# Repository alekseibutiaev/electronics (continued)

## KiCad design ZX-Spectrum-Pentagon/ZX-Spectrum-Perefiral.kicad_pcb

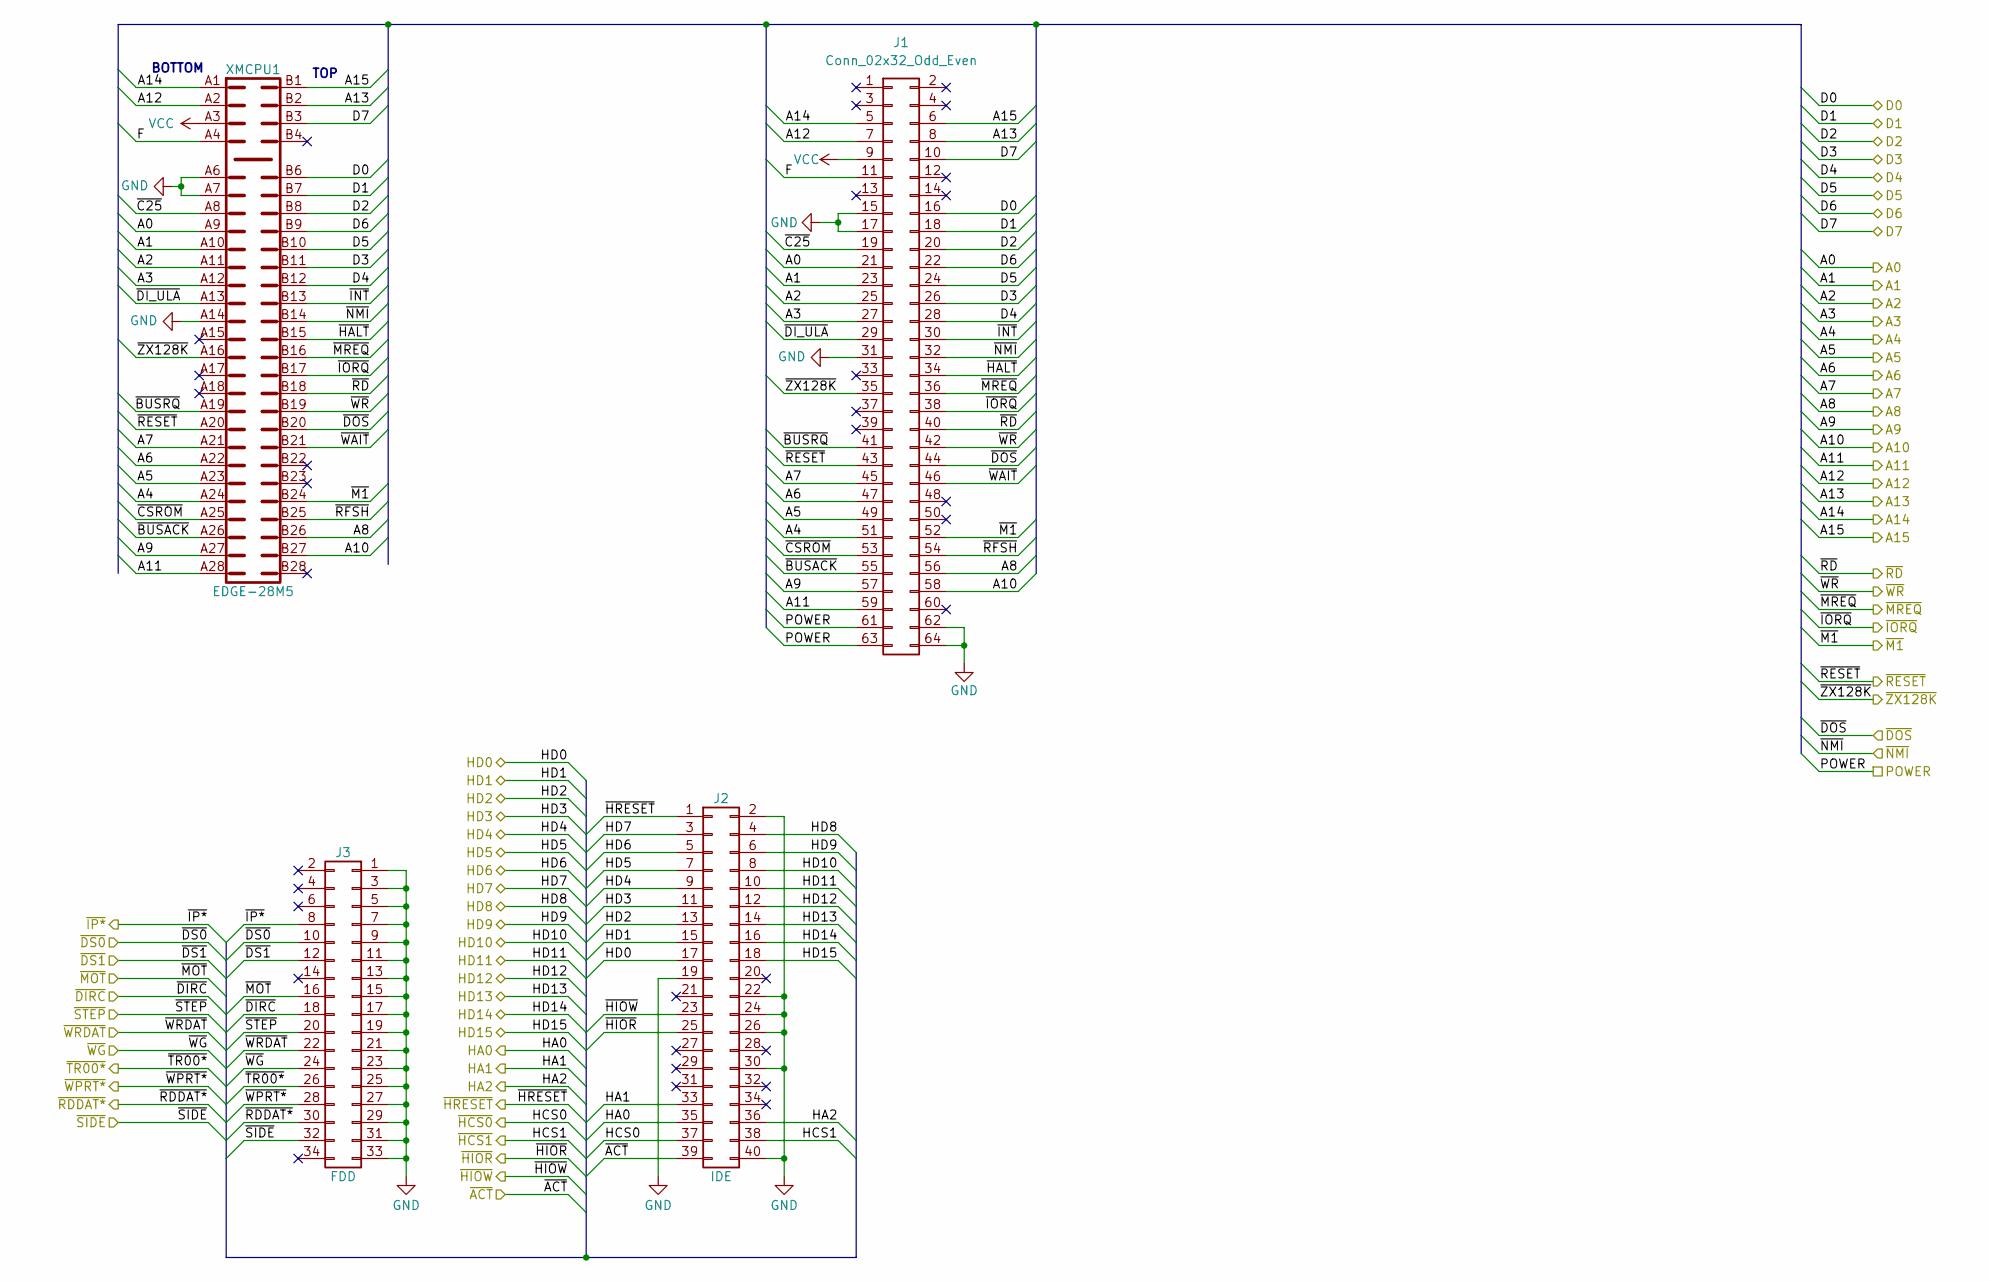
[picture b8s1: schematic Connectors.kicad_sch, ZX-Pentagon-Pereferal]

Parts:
J1: Conn_02x32_Odd_Even; PinSocket_2x32_P2.54mm_Vertical
J2: IDE; IDC-Header_2x20_P2.54mm_Vertical
J3: FDD; IDC-Header_2x17_P2.54mm_Vertical
XMCPU1: EDGE-28M5; EDGE_28M5-2.54

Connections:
/A0: J1.21, XMCPU1.A9; also elsewhere on the board
/A1: J1.23, XMCPU1.A10; also elsewhere on the board
/A2: J1.25, XMCPU1.A11; also elsewhere on the board
/A3: J1.27, XMCPU1.A12; also elsewhere on the board
/A4: J1.51, XMCPU1.A24; also elsewhere on the board
/A5: J1.49, XMCPU1.A23; also elsewhere on the board
/A6: J1.47, XMCPU1.A22; also elsewhere on the board
/A7: J1.45, XMCPU1.A21; also elsewhere on the board
/A8: J1.56, XMCPU1.B26; also elsewhere on the board
/A9: J1.57, XMCPU1.A27; also elsewhere on the board
/A10: J1.58, XMCPU1.B27; also elsewhere on the board
/A11: J1.59, XMCPU1.A28; also elsewhere on the board
/A12: J1.7, XMCPU1.A2; also elsewhere on the board
/A13: J1.8, XMCPU1.B2; also elsewhere on the board
/A14: J1.5, XMCPU1.A1; also elsewhere on the board
/A15: J1.6, XMCPU1.B1; also elsewhere on the board
/Connectors/F: J1.11, XMCPU1.A4
/Connectors/~BUSACK: J1.55, XMCPU1.A26
/Connectors/~BUSRQ: J1.41, XMCPU1.A19
/Connectors/~C25: J1.19, XMCPU1.A8
/Connectors/~CSROM: J1.53, XMCPU1.A25
/Connectors/~DI_ULA: J1.29, XMCPU1.A13
/Connectors/~HALT: J1.34, XMCPU1.B15
/Connectors/~INT: J1.30, XMCPU1.B13
/Connectors/~RFSH: J1.54, XMCPU1.B25
/Connectors/~WAIT: J1.46, XMCPU1.B21
/D0: J1.16, XMCPU1.B6; also elsewhere on the board
/D1: J1.18, XMCPU1.B7; also elsewhere on the board
/D2: J1.20, XMCPU1.B8; also elsewhere on the board
/D3: J1.26, XMCPU1.B11; also elsewhere on the board
/D4: J1.28, XMCPU1.B12; also elsewhere on the board
/D5: J1.24, XMCPU1.B10; also elsewhere on the board
/D6: J1.22, XMCPU1.B9; also elsewhere on the board
/D7: J1.10, XMCPU1.B3; also elsewhere on the board
/HA0: J2.35; also elsewhere on the board
/HA1: J2.33; also elsewhere on the board
/HA2: J2.36; also elsewhere on the board
/HD0: J2.17; also elsewhere on the board
/HD1: J2.15; also elsewhere on the board
/HD2: J2.13; also elsewhere on the board
/HD3: J2.11; also elsewhere on the board
/HD4: J2.9; also elsewhere on the board
/HD5: J2.7; also elsewhere on the board
/HD6: J2.5; also elsewhere on the board
/HD7: J2.3; also elsewhere on the board
/HD8: J2.4; also elsewhere on the board
/HD9: J2.6; also elsewhere on the board
/HD10: J2.8; also elsewhere on the board
/HD11: J2.10; also elsewhere on the board
/HD12: J2.12; also elsewhere on the board
/HD13: J2.14; also elsewhere on the board
/HD14: J2.16; also elsewhere on the board
/HD15: J2.18; also elsewhere on the board
/~ACT: J2.39; also elsewhere on the board
/~DIRC: J3.18; also elsewhere on the board
/~DOS: J1.44, XMCPU1.B20; also elsewhere on the board
/~DS0: J3.10; also elsewhere on the board
/~DS1: J3.12; also elsewhere on the board
/~HCS0: J2.37; also elsewhere on the board
/~HCS1: J2.38; also elsewhere on the board
/~HIOR: J2.25; also elsewhere on the board
/~HIOW: J2.23; also elsewhere on the board
/~HRESET: J2.1; also elsewhere on the board
/~IORQ: J1.38, XMCPU1.B17; also elsewhere on the board
/~IP*: J3.8; also elsewhere on the board
/~M1: J1.52, XMCPU1.B24; also elsewhere on the board
/~MOT: J3.16; also elsewhere on the board
/~MREQ: J1.36, XMCPU1.B16; also elsewhere on the board
/~NMI: J1.32, XMCPU1.B14; also elsewhere on the board
/~RDDAT*: J3.30; also elsewhere on the board
/~RD: J1.40, XMCPU1.B18; also elsewhere on the board
/~RESET: J1.43, XMCPU1.A20; also elsewhere on the board
/~SIDE: J3.32; also elsewhere on the board
/~STEP: J3.20; also elsewhere on the board
/~TR00*: J3.26; also elsewhere on the board
/~WG: J3.24; also elsewhere on the board
/~WPRT*: J3.28; also elsewhere on the board
/~WRDAT: J3.22; also elsewhere on the board
/~WR: J1.42, XMCPU1.B19; also elsewhere on the board
/~ZX128: J1.35, XMCPU1.A16; also elsewhere on the board
GND: J1.15, J1.17, J1.31, J1.62, J1.64, J2.2, J2.19, J2.22, J2.24, J2.26, J2.30, J2.40, J3.1, J3.3, J3.5, J3.7, J3.9, J3.11, J3.13, J3.15, J3.17, J3.19, J3.21, J3.23, J3.25, J3.27, J3.29, J3.31, J3.33, XMCPU1.A6, XMCPU1.A7, XMCPU1.A14; also elsewhere on the board
POWER: J1.61, J1.63; also elsewhere on the board
VCC: J1.9, XMCPU1.A3; also elsewhere on the board

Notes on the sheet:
TOP
BOTTOM

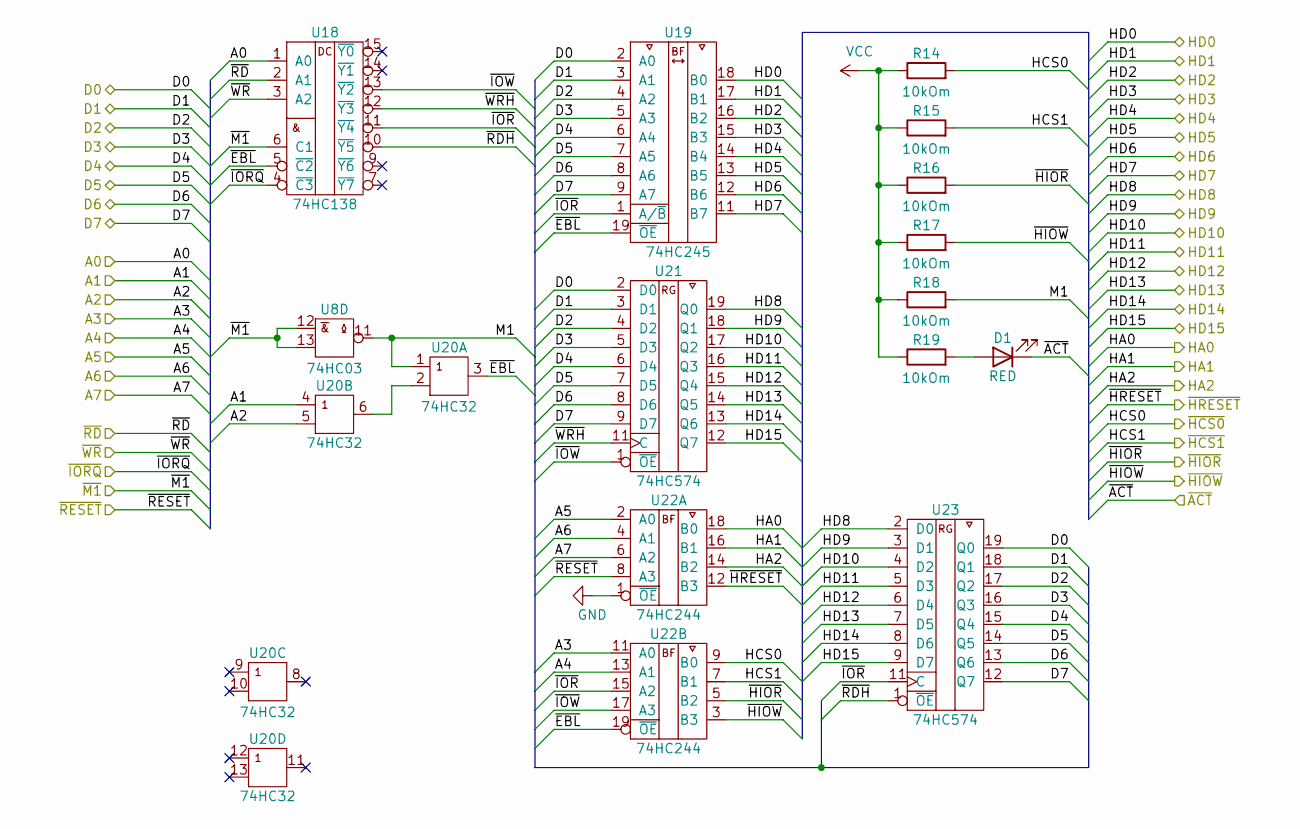
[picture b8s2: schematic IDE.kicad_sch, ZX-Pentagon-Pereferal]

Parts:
D1: RED; D_0805_2012Metric
R14, R15, R16, R17, R18, R19: 10kOm; R_0805_2012Metric
U8: 74HC03; DIP-14_W7.62mm
U18: 74HC138; DIP-16_W7.62mm
U19: 74HC245; DIP-20_W7.62mm
U20: 74HC32; DIP-14_W7.62mm
U21, U23: 74HC574; DIP-20_W7.62mm
U22: 74HC244; DIP-20_W7.62mm

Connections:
/A0: U18.1 (A0); also elsewhere on the board
/A1: U20.4 (A); also elsewhere on the board
/A2: U20.5 (B); also elsewhere on the board
/A3: U22.11 (A0); also elsewhere on the board
/A4: U22.13 (A1); also elsewhere on the board
/A5: U22.2 (A0); also elsewhere on the board
/A6: U22.4 (A1); also elsewhere on the board
/A7: U22.6 (A2); also elsewhere on the board
/D0: U19.2 (A0), U21.2 (D0), U23.19 (Q0); also elsewhere on the board
/D1: U19.3 (A1), U21.3 (D1), U23.18 (Q1); also elsewhere on the board
/D2: U19.4 (A2), U21.4 (D2), U23.17 (Q2); also elsewhere on the board
/D3: U19.5 (A3), U21.5 (D3), U23.16 (Q3); also elsewhere on the board
/D4: U19.6 (A4), U21.6 (D4), U23.15 (Q4); also elsewhere on the board
/D5: U19.7 (A5), U21.7 (D5), U23.14 (Q5); also elsewhere on the board
/D6: U19.8 (A6), U21.8 (D6), U23.13 (Q6); also elsewhere on the board
/D7: U19.9 (A7), U21.9 (D7), U23.12 (Q7); also elsewhere on the board
/HA0: U22.18 (B0); also elsewhere on the board
/HA1: U22.16 (B1); also elsewhere on the board
/HA2: U22.14 (B2); also elsewhere on the board
/HD0: U19.18 (B0); also elsewhere on the board
/HD1: U19.17 (B1); also elsewhere on the board
/HD2: U19.16 (B2); also elsewhere on the board
/HD3: U19.15 (B3); also elsewhere on the board
/HD4: U19.14 (B4); also elsewhere on the board
/HD5: U19.13 (B5); also elsewhere on the board
/HD6: U19.12 (B6); also elsewhere on the board
/HD7: U19.11 (B7); also elsewhere on the board
/HD8: U21.19 (Q0), U23.2 (D0); also elsewhere on the board
/HD9: U21.18 (Q1), U23.3 (D1); also elsewhere on the board
/HD10: U21.17 (Q2), U23.4 (D2); also elsewhere on the board
/HD11: U21.16 (Q3), U23.5 (D3); also elsewhere on the board
/HD12: U21.15 (Q4), U23.6 (D4); also elsewhere on the board
/HD13: U21.14 (Q5), U23.7 (D5); also elsewhere on the board
/HD14: U21.13 (Q6), U23.8 (D6); also elsewhere on the board
/HD15: U21.12 (Q7), U23.9 (D7); also elsewhere on the board
/IDE/M1: R18.2, U8.11 (~Y), U20.1 (A)
/IDE/~EBL: U18.5 (~C2), U19.19 (~OE), U20.3 (Y), U22.19 (~OE)
/IDE/~IOR: U18.11 (~Y4), U19.1 (A/~B), U22.15 (A2), U23.11 (C)
/IDE/~IOW: U18.13 (~Y2), U21.1 (~OE), U22.17 (A3)
/IDE/~RDH: U18.10 (~Y5), U23.1 (~OE)
/IDE/~WRH: U18.12 (~Y3), U21.11 (C)
/~ACT: D1.1 (K); also elsewhere on the board
/~HCS0: R14.2, U22.9 (B0); also elsewhere on the board
/~HCS1: R15.2, U22.7 (B1); also elsewhere on the board
/~HIOR: R16.2, U22.5 (B2); also elsewhere on the board
/~HIOW: R17.2, U22.3 (B3); also elsewhere on the board
/~HRESET: U22.12 (B3); also elsewhere on the board
/~IORQ: U18.4 (~C3); also elsewhere on the board
/~M1: U8.12 (A), U8.13 (B), U18.6 (C1); also elsewhere on the board
/~RD: U18.2 (A1); also elsewhere on the board
/~RESET: U22.8 (A3); also elsewhere on the board
/~WR: U18.3 (A2); also elsewhere on the board
GND: U8.7 (GND), U18.8 (GND), U19.10 (GND), U20.7 (GND), U21.10 (GND), U22.1 (~OE), U22.10 (GND), U23.10 (GND); also elsewhere on the board
unnamed: D1.2 (A), R19.2
unnamed: U20.2 (B), U20.6 (Y)
VCC: R14.1, R15.1, R16.1, R17.1, R18.1, R19.1, U8.14 (VCC), U18.16 (VCC), U19.20 (VCC), U20.14 (VCC), U21.20 (VCC), U22.20 (VCC), U23.20 (VCC); also elsewhere on the board

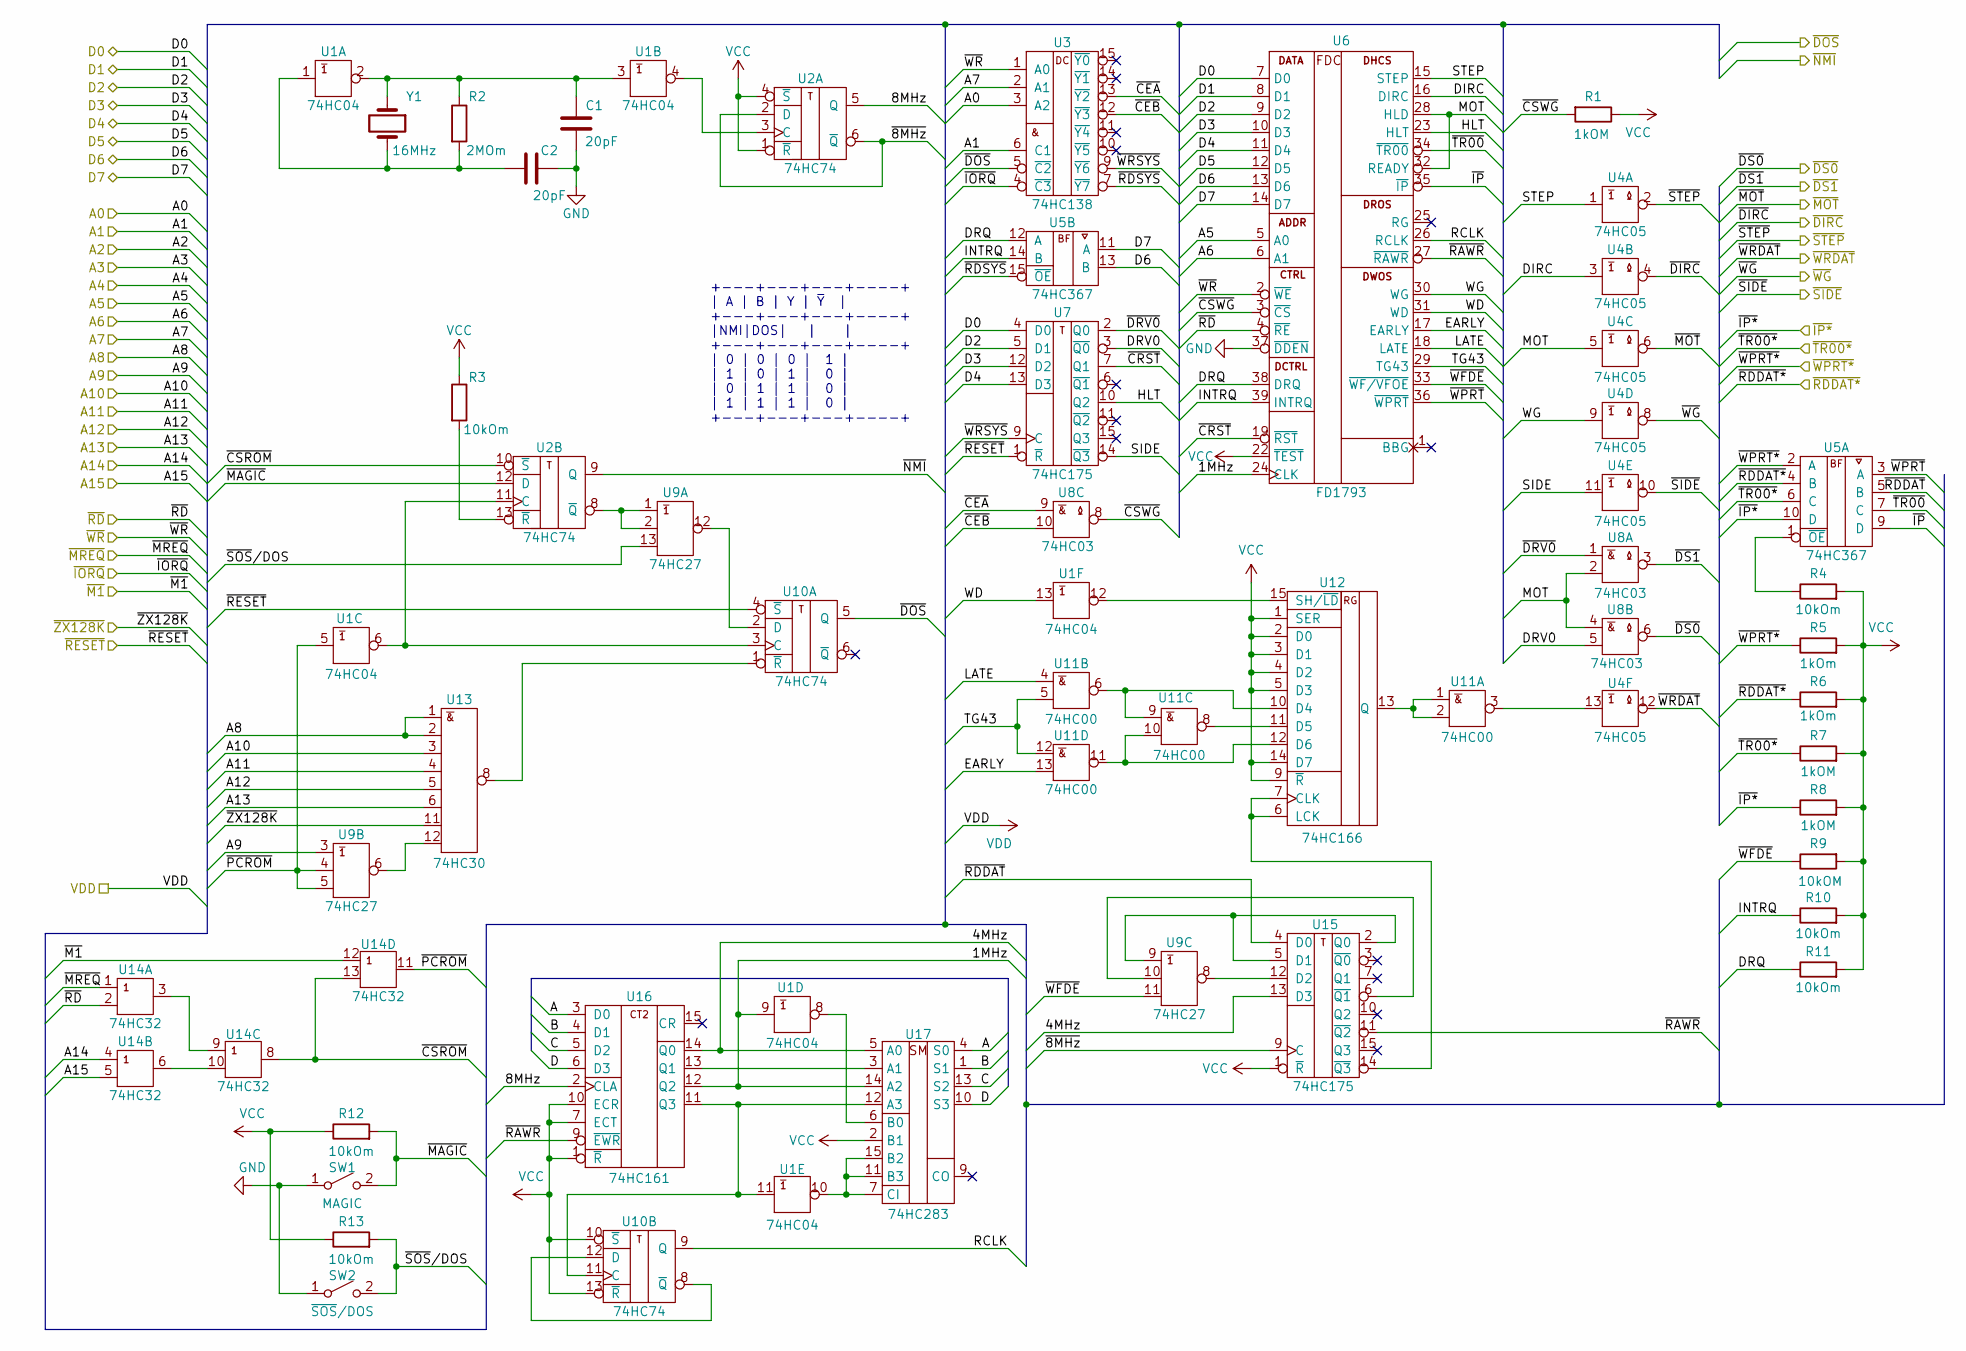
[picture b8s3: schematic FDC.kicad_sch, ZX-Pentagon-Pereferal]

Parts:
C1, C2: 20pF; C_0805_2012Metric_Pad1.18x1.45mm_HandSolder
R1, R7, R8: 1kOM; R_0805_2012Metric
R2: 2MOm; R_0805_2012Metric_Pad1.20x1.40mm_HandSolder
R3, R4, R10, R11, R12, R13: 10kOm; R_0805_2012Metric
R5, R6: 1kOm; R_0805_2012Metric
R9: 10kOM; R_0805_2012Metric
SW1: MAGIC; SW_Tactile_SPST_Angled_PTS645Vx39-2LFS
SW2: ~{SOS}/DOS; SW_Tactile_SPST_Angled_PTS645Vx39-2LFS
U1: 74HC04; DIP-14_W7.62mm
U2, U10: 74HC74; DIP-14_W7.62mm
U3: 74HC138; DIP-16_W7.62mm
U4: 74HC05; DIP-14_W7.62mm
U5: 74HC367; DIP-16_W7.62mm
U6: FD1793; DIP-40_W15.24mm
U7, U15: 74HC175; DIP-16_W7.62mm
U8: 74HC03; DIP-14_W7.62mm
U9: 74HC27; DIP-14_W7.62mm
U11: 74HC00; DIP-14_W7.62mm
U12: 74HC166; DIP-16_W7.62mm
U13: 74HC30; DIP-14_W7.62mm
U14: 74HC32; DIP-14_W7.62mm
U16: 74HC161; DIP-16_W7.62mm
U17: 74HC283; DIP-16_W7.62mm
Y1: 16MHz; Crystal_HC49-U_Vertical

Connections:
/A0: U3.3 (A2); also elsewhere on the board
/A1: U3.6 (C1); also elsewhere on the board
/A5: U6.5 (A0); also elsewhere on the board
/A6: U6.6 (A1); also elsewhere on the board
/A7: U3.2 (A1); also elsewhere on the board
/A8: U13.1 (A), U13.2 (B); also elsewhere on the board
/A9: U9.3 (A); also elsewhere on the board
/A10: U13.3 (C); also elsewhere on the board
/A11: U13.4 (D); also elsewhere on the board
/A12: U13.5 (E); also elsewhere on the board
/A13: U13.6 (F); also elsewhere on the board
/A14: U14.4 (A); also elsewhere on the board
/A15: U14.5 (B); also elsewhere on the board
/D0: U6.7 (D0), U7.4 (D0); also elsewhere on the board
/D1: U6.8 (D1); also elsewhere on the board
/D2: U6.9 (D2), U7.5 (D1); also elsewhere on the board
/D3: U6.10 (D3), U7.12 (D2); also elsewhere on the board
/D4: U6.11 (D4), U7.13 (D3); also elsewhere on the board
/D5: U6.12 (D5); also elsewhere on the board
/D6: U5.13 (B), U6.13 (D6); also elsewhere on the board
/D7: U5.11 (A), U6.14 (D7); also elsewhere on the board
/FDC/1MHz: U1.9 (A), U6.24 (CLK), U16.12 (Q2), U17.14 (A2)
/FDC/4MHz: U15.13 (D3), U16.14 (Q0), U17.5 (A0)
/FDC/8MHz: U2.5 (Q), U16.2 (CLA)
/FDC/A: U16.3 (D0), U17.4 (S0)
/FDC/B: U16.4 (D1), U17.1 (S1)
/FDC/C: U16.5 (D2), U17.13 (S2)
/FDC/D: U16.6 (D3), U17.10 (S3)
/FDC/DIRC: U4.3 (A), U6.16 (DIRC)
/FDC/DRQ: R11.1, U5.12 (A), U6.38 (DRQ)
/FDC/DRV0: U7.3 (~Q0), U8.5 (B)
/FDC/EARLY: U6.17 (EARLY), U11.13 (B)
/FDC/HLT: U6.23 (HLT), U7.10 (Q2)
/FDC/INTRQ: R10.1, U5.14 (B), U6.39 (INTRQ)
/FDC/LATE: U6.18 (LATE), U11.4 (A)
/FDC/MOT: U4.5 (A), U6.28 (HLD), U6.32 (READY), U8.2 (B), U8.4 (A)
/FDC/RCLK: U6.26 (RCLK), U10.9 (Q)
/FDC/SIDE: U4.11 (A), U7.14 (~Q3)
/FDC/STEP: U4.1 (A), U6.15 (STEP)
/FDC/TG43: U6.29 (TG43), U11.5 (B), U11.12 (A)
/FDC/WD: U1.13 (A), U6.31 (WD)
/FDC/WG: U4.9 (A), U6.30 (WG)
/FDC/~8MHz: U2.2 (D), U2.6 (~Q), U15.9 (C)
/FDC/~CEA: U3.13 (~Y2), U8.9 (A)
/FDC/~CEB: U3.12 (~Y3), U8.10 (B)
/FDC/~CRST: U6.19 (~RST), U7.7 (Q1)
/FDC/~CSROM: U2.10 (~S), U14.8 (Y), U14.13 (B)
/FDC/~CSWG: R1.2, U6.3 (~CS), U8.8 (~Y)
/FDC/~DRV0: U7.2 (Q0), U8.1 (A)
/FDC/~IP: U5.9 (D), U6.35 (~IP)
/FDC/~MAGIC: R12.2, SW1.2 (B), U2.12 (D)
/FDC/~PCROM: U1.5 (A), U9.4 (B), U9.5 (C), U14.11 (Y)
/FDC/~RAWR: U6.27 (~RAWR), U15.11 (~Q2), U16.9 (~EWR)
/FDC/~RDDAT: U5.5 (B), U15.4 (D0)
/FDC/~RDSYS: U3.7 (~Y7), U5.15 (~OE)
/FDC/~SOS/DOS: R13.2, SW2.2 (B), U9.13 (C)
/FDC/~TR00: U5.7 (C), U6.34 (~TR00)
/FDC/~WFDE: R9.1, U6.33 (~WF/VFOE), U9.11 (C)
/FDC/~WPRT: U5.3 (A), U6.36 (~WPRT)
/FDC/~WRSYS: U3.9 (~Y6), U7.9 (C)
/~DIRC: U4.4 (~Y); also elsewhere on the board
/~DOS: U3.5 (~C2), U10.5 (Q); also elsewhere on the board
/~DS0: U8.6 (~Y); also elsewhere on the board
/~DS1: U8.3 (~Y); also elsewhere on the board
/~IORQ: U3.4 (~C3); also elsewhere on the board
/~IP*: R8.1, U5.10 (D); also elsewhere on the board
/~M1: U14.12 (A); also elsewhere on the board
/~MOT: U4.6 (~Y); also elsewhere on the board
/~MREQ: U14.1 (A); also elsewhere on the board
/~NMI: U2.9 (Q); also elsewhere on the board
/~RDDAT*: R6.1, U5.4 (B); also elsewhere on the board
/~RD: U6.4 (~RE), U14.2 (B); also elsewhere on the board
/~RESET: U7.1 (~R), U10.4 (~S); also elsewhere on the board
/~SIDE: U4.10 (~Y); also elsewhere on the board
/~STEP: U4.2 (~Y); also elsewhere on the board
/~TR00*: R7.1, U5.6 (C); also elsewhere on the board
/~WG: U4.8 (~Y); also elsewhere on the board
/~WPRT*: R5.1, U5.2 (A); also elsewhere on the board
/~WRDAT: U4.12 (~Y); also elsewhere on the board
/~WR: U3.1 (A0), U6.2 (~WE); also elsewhere on the board
/~ZX128: U13.11 (G); also elsewhere on the board
GND: C1.2, C2.2, SW1.1 (A), SW2.1 (A), U1.7 (GND), U2.7 (GND), U3.8 (GND), U4.7 (GND), U5.8 (GND), U6.20 (GND), U6.37 (~DDEN), U7.8 (GND), U8.7 (GND), U9.7 (GND), U10.7 (GND), U11.7 (GND), U12.8 (GND), U13.7 (GND), U14.7 (GND), U15.8 (GND), U16.8 (GND), U17.8 (GND); also elsewhere on the board
unnamed: C2.1, R2.2, U1.1 (A), Y1.2
unnamed: C1.1, R2.1, U1.2 (~Y), U1.3 (A), Y1.1
unnamed: U1.4 (~Y), U2.3 (C)
unnamed: U2.8 (~Q), U9.1 (A), U9.2 (B)
unnamed: R3.2, U2.13 (~R)
unnamed: R4.1, U5.1 (~OE)
unnamed: U1.6 (~Y), U2.11 (C), U10.3 (C)
unnamed: U9.12 (~Y), U10.2 (D)
unnamed: U10.1 (~R), U13.8 (~Y)
unnamed: U1.11 (A), U10.11 (C), U16.11 (Q3), U17.12 (A3)
unnamed: U10.8 (~Q), U10.12 (D)
unnamed: U11.1 (A), U11.2 (B), U12.13 (Q)
unnamed: U4.13 (A), U11.3 (~Y)
unnamed: U11.6 (~Y), U11.9 (A), U12.10 (D4)
unnamed: U11.10 (B), U11.11 (~Y), U12.12 (D6)
unnamed: U11.8 (~Y), U12.11 (D5)
unnamed: U12.6 (LCK), U12.7 (CLK), U15.14 (~Q3)
unnamed: U1.12 (~Y), U12.15 (SH/~LD)
unnamed: U9.6 (~Y), U13.12 (H)
unnamed: U14.3 (Y), U14.9 (A)
unnamed: U14.6 (Y), U14.10 (B)
unnamed: U9.9 (A), U15.2 (Q0), U15.5 (D1)
unnamed: U9.8 (~Y), U15.12 (D2)
unnamed: U9.10 (B), U15.6 (~Q1)
unnamed: U16.13 (Q1), U17.3 (A1)
unnamed: U1.8 (~Y), U17.6 (B0)
unnamed: U1.10 (~Y), U17.7 (CI), U17.11 (B3), U17.15 (B2)
VCC: R1.1, R3.1, R4.2, R5.2, R6.2, R7.2, R8.2, R9.2, R10.2, R11.2, R12.1, R13.1, U1.14 (VCC), U2.1 (~R), U2.4 (~S), U2.14 (VCC), U3.16 (VCC), U4.14 (VCC), U5.16 (VCC), U6.21 (VCC), U6.22 (~TEST), U7.16 (VCC), U8.14 (VCC), U9.14 (VCC), U10.10 (~S), U10.13 (~R), U10.14 (VCC), U11.14 (VCC), U12.1 (SER), U12.2 (D0), U12.3 (D1), U12.4 (D2), U12.5 (D3), U12.9 (~R), U12.14 (D7), U12.16 (VCC), U13.14 (VCC), U14.14 (VCC), U15.1 (~R), U15.16 (VCC), U16.1 (~R), U16.7 (ECT), U16.10 (ECR), U16.16 (VCC), U17.2 (B1), U17.16 (VCC); also elsewhere on the board
VDD: U6.40 (VDD); also elsewhere on the board

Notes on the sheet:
+---+---+---+----+ | A | B | Y | ~{Y} | +---+---+---+----+ |NMI|DOS| | | +---+---+---+----+ | 0 | 0 | 0 | 1 | | 1 | 0 | 1 | 0 | | 0 | 1 | 1 | 0 | | 1 | 1 | 1 | 0 | +---+---+---+----+

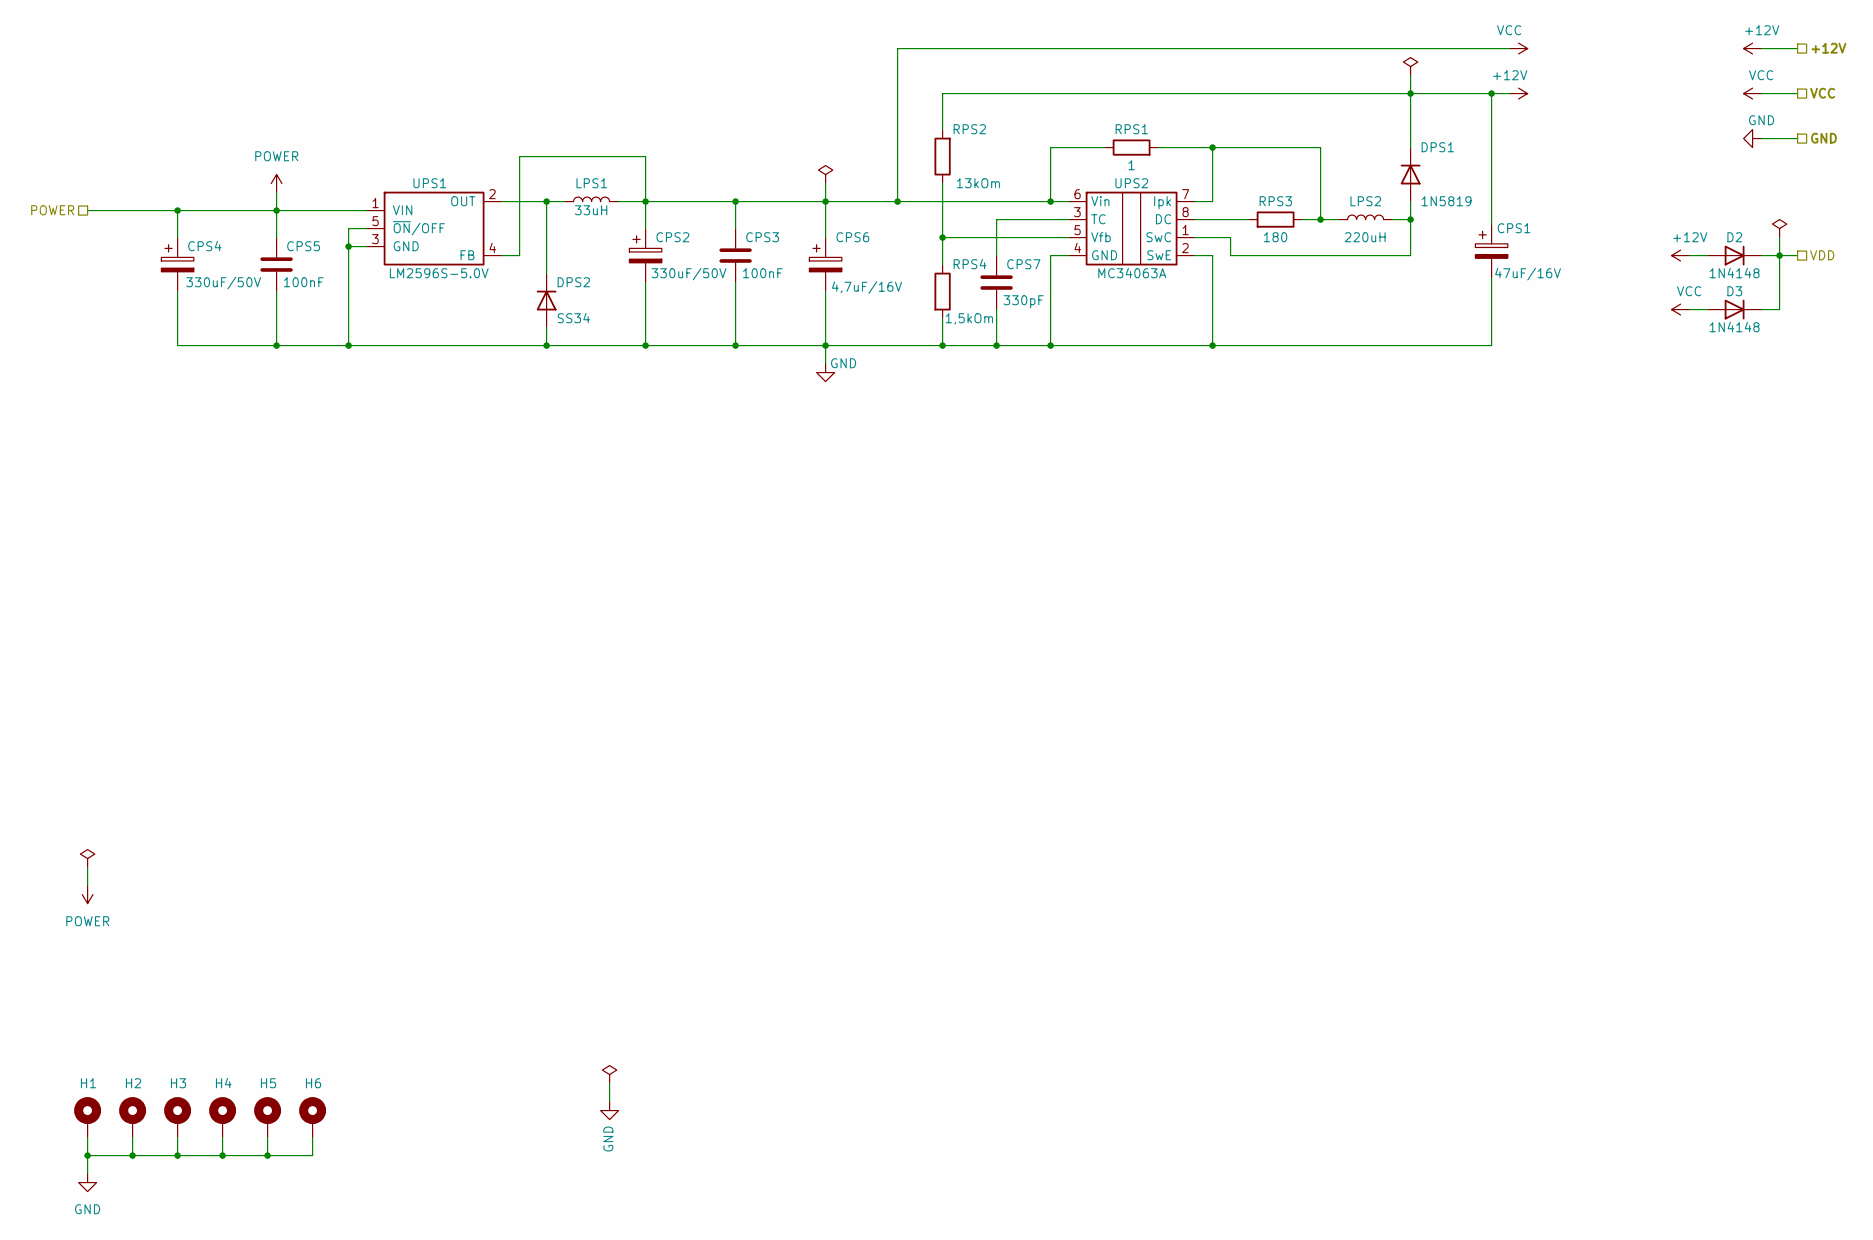
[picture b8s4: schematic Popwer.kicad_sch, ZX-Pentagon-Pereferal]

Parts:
CPS1: 47uF/16V; CP_EIA-3216-18_Kemet-A_Pad1.58x1.35mm_HandSolder
CPS2, CPS4: 330uF/50V; CP_EIA-7343-31_Kemet-D_Pad2.25x2.55mm_HandSolder
CPS3, CPS5: 100nF; C_0805_2012Metric_Pad1.18x1.45mm_HandSolder
CPS6: 4,7uF/16V; CP_EIA-3216-18_Kemet-A_Pad1.58x1.35mm_HandSolder
CPS7: 330pF; C_0805_2012Metric_Pad1.18x1.45mm_HandSolder
D2, D3: 1N4148; D_MiniMELF
DPS1: 1N5819; D_SOD-323_HandSoldering
DPS2: SS34; D_SMA
H1, H2, H3, H4, H5, H6: MountingHole_Pad; MountingHole_3.2mm_M3_Pad_Via
LPS1: 33uH; L_12x12mm_H6mm
LPS2: 220uH; CD43
RPS1: 1; R_0805_2012Metric_Pad1.20x1.40mm_HandSolder
RPS2: 13kOm; R_0805_2012Metric_Pad1.20x1.40mm_HandSolder
RPS3: 180; R_0805_2012Metric_Pad1.20x1.40mm_HandSolder
RPS4: 1,5kOm; R_0805_2012Metric_Pad1.20x1.40mm_HandSolder
UPS1: LM2596S-5.0V; TO-263-5_TabPin3
UPS2: MC34063A; SO-8_3.9x4.9mm_P1.27mm

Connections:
+12V: CPS1.1, D2.2 (A), DPS1.1 (K), RPS2.2
GND: CPS1.2, CPS2.2, CPS3.2, CPS4.2, CPS5.2, CPS6.2, CPS7.2, DPS2.2 (A), H1.1, H2.1, H3.1, H4.1, H5.1, H6.1, RPS4.2, UPS1.3 (GND), UPS1.5 (~ON/OFF), UPS2.2 (SwE), UPS2.4 (GND); also elsewhere on the board
unnamed: DPS1.2 (A), LPS2.1, UPS2.1 (SwC)
unnamed: DPS2.1 (K), LPS1.1, UPS1.2 (OUT)
unnamed: RPS3.2, UPS2.8 (DC)
unnamed: LPS2.2, RPS1.2, RPS3.1, UPS2.7 (Ipk)
unnamed: CPS7.1, UPS2.3 (TC)
unnamed: RPS2.1, RPS4.1, UPS2.5 (Vfb)
POWER: CPS4.1, CPS5.1, UPS1.1 (VIN); also elsewhere on the board
VCC: CPS2.1, CPS3.1, CPS6.1, D3.2 (A), LPS1.2, RPS1.1, UPS1.4 (FB), UPS2.6 (Vin); also elsewhere on the board
VDD: D2.1 (K), D3.1 (K); also elsewhere on the board

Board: 2 copper layers, 77 parts (0 on the bottom side), 165 nets, no tracks yet.

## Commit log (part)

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2022-07-27 tracing generator
2022-07-27 restore generator
2022-08-02 change some unitand pins tracing generator
2022-08-03 full tracing
2022-08-03 fix DRC
2022-08-03 some changes
2022-08-03 stage 1
2022-08-03 both side
2022-08-03 fix power connector
2022-08-03 refil zones
2022-08-04 fix some warnings
2022-08-04 some fix
2022-08-04 restore GND connecter
2022-08-04 chance footprint for botton a lot of slall fixed
2022-08-04 fix reacing
2022-08-07 add some documentation
2022-08-08 some improvment
2022-08-08 select rom by 64kByte improve tracing
2022-08-09 improve tracing
2022-08-10 small improvment
2022-08-10 recinnect RA15 RA16 RA17 RA18
2022-08-10 some trace
2022-08-10 reptacing AYCLK MA17 RST sime improvment
2022-08-11 improve transaction
2022-08-16 some improve
2022-08-20 migrate to KiCad6
2022-08-20 update silk layer
2022-08-20 update foorprint and tracing for new footprint
2022-08-20 add demension lone
2022-08-23 update Z80 cpu symbol update button footprint
2022-08-24 update footprint AD724
2022-09-08 customizing footprint audio jack 3.5 and change up position in PCB
2022-09-08 change up foot print for audio jack 3.5mm and QG1
2022-09-09 Fix generator for HC
2022-09-09 update project
2022-09-09 tracint
2022-09-11 re annotate and retracing some think
2022-09-12 some updare
2022-09-14 fix VSYNC HSYNC
2022-09-16 FIX rgb add selector 4FSC/FSC
2022-09-20 modefie 4FSC
2022-09-29 add cabel schema improve pcb
2022-09-29 fix generation script
2022-09-29 test pcb
2022-09-29 update edge connector
2022-09-29 some update
2022-09-29 improve script
2022-09-29 improve edge
2022-09-29 Fix cupper zone
2022-10-01 fix screen address
2022-10-01 add debug code
2022-10-01 update ignore list
2022-10-03 add feporttest.asm
2022-10-03 improve companen library
2022-10-03 non functional changes
2022-10-03 update symbol library
2022-10-03 update symbol
2022-10-03 reset annotate
2022-10-06 rename file fix 74XX192 74xx193
2022-10-06 update symbol add IC position Layer
2022-10-06 add Mini DIN connectors MD-30, MD-40, MD-60, MD-70, MD-80, MD-90
2022-10-06 add datasheet
2022-10-07 improve libraty
2022-10-08 uodare Video Encoder
2022-10-08 modefie footprint for MD-X0SM* modefie video
2022-10-08 add some footprint
2022-10-09 move switch descriptor
2022-10-09 fix selecter memory page MX0 MX1
2022-10-09 modefied memoru address select
2022-10-10 some tracing update
2022-10-11 add emulator
2022-10-13 migrate to logissim-evolution
2022-10-13 rename
2022-10-13 add Memory Sharing module
2022-10-13 unfiil zone
2022-10-13 unfill zone
2022-10-13 Lock all footprint
2022-10-13 update emilator
2022-10-13 Fix SN7493 & SN74393
2022-10-14 add tunel for adedress multiplexor
2022-10-14 change font for tumel
2022-10-25 add color test
2022-10-26 improve GAL port encoder
2022-10-26 update tracing
2022-10-26 Add MountingHole
2022-10-26 update annotate for pcb use Mounting Hole
2022-10-26 Silk layer update
2022-11-08 add footprint inductor CD start ZX-Specttrum keyboard
2022-11-11 migrete from LTC1262 to MC32063
2022-11-13 PULLUP ~DI_ULA
2022-11-14 add pullup for ~{DI_ULA}
2022-11-17 start ZX_keyboard project
2022-11-19 start ZX-keyboard device
2022-11-21 update information
2022-11-22 add connector sheet
2022-11-28 improve zx_keyboard schematic
2022-11-28 improve schematic
2022-11-30 update and fix schematic
2022-11-30 add footprint for D1 D2 MCU unit
2022-11-30 rename from MOIS to MOSI
2022-11-30 update schema trace pcb
2022-12-01 update schematic and pcb
2022-12-07 update pcb
2022-12-07 improve inductor footpriint
2022-12-08 add 3d models
2022-12-08 fix keyboard connectors
2022-12-09 first release
2022-12-16 update schematic
2022-12-17 non function cnange
2022-12-17 move companents: Tape Input & 12V power
2022-12-17 add 3d model for power inductor
2022-12-18 move tape in and step-up unit
2022-12-18 use 2 line connector for AY_IO reposition and retacing power step_up sources and tape input
2022-12-18 Improve User Defenition layer
2022-12-18 improve silj layer
2022-12-18 add connector for HDMI addapter
2022-12-19 tracing connector fo HDMI adapter
2022-12-19 update user defenition
2022-12-19 move U34
2022-12-19 move U32
2022-12-19 move IC
2022-12-19 change from SN74HC93 to SN74HC393
2022-12-19 fix 74XX393
2022-12-19 update symbol 74HC393
2022-12-27 tracing
2022-12-28 update keyboard pcb
2023-01-10 add verilog library sn74lib and test bench
2023-01-12 add sn74xx193
2023-01-12 add SN74XX393
2023-01-12 add circuit sn74xx193
2023-01-12 merge
2023-01-12 use foot print D_MiniMELF for diode zinner
2023-01-12 add power for keyboard
2023-01-12 update User.Drawings Layer
2023-01-19 teracing and refactoring connectors
2023-01-19 change up diode foot print to SOD-80
2023-01-20 update user driwing lauer
2023-01-21 update footprint for diode
2023-01-23 start stlink
2023-01-29 improve schematic of stlink_v2
2023-01-31 add 74LVCC3245
2023-02-08 update 74xx3245
2023-03-02 update schema
2023-03-16 update schenatic and pcb
2023-03-17 fix footprint
2023-03-17 update schema and pcb
2023-03-31 add 60 pin connector for top lever
2023-04-23 upddate capacitor values
2023-04-24 fix schematic and pcb
2023-04-30 update add power controller
2023-05-04 update zx_keyboard pcb
2023-05-04 pcb update
2023-05-04 lock unlocked files
2023-05-04 restore zx_ketboard_pcb_v0.3
2023-05-13 Add firmware
2023-05-20 Silck layer
2023-05-23 add firmware andwakeup
2023-05-27 Add power filter create pcb
2023-05-27 non function changes
2023-05-27 add ~{RESET} signal to keyboard
2023-06-09 add second level delete TYPETTL
2023-07-05 non functional updaate
2023-07-06 add bootloader add firmware for STLink_V2-1
2023-07-06 add connector doc
2023-07-06 change resistor value
2023-07-07 fix resistor annatation
2023-07-07 non function change
2023-07-08 non functional change
2023-07-10 add firmware flashing info
2023-07-11 migrate to KiCAD 7
2023-07-18 add 3d model add demension
2023-07-18 add mounting hole for user layer
2023-07-18 add demension line
2023-07-21 improve PCB User.Drowing & User.Comment
2023-07-21 sime update
2023-07-30 change up SN74HC541 to SN74HC245
2023-07-30 add housing
2023-08-01 rename some net
2023-08-01 Add schema and non functional chanjes
2023-08-09 add GND connection change User.Driwings layer
2023-08-09 git update housing
2023-08-09 start new project Irrigation
2023-08-12 modefie model
2023-08-16 add fpasl documentation
2023-08-27 fix 74IEC library Add stlink connector info delete unused picture update symbols for ZX-Spectrum-Pentagon
2023-08-27 lock free footprint
2023-08-27 migrate to mini_melf
2023-09-07 add companent list
2023-09-08 add project test add Makefile for wirelog add verilog wrapper for kicad
2023-09-21 fix 12V power
2023-10-11 fix tape input
2023-10-14 improve type in schema improve PAL video encoder
2023-10-14 update user comments
2023-10-17 update Resistors value
2023-10-17 update library
2023-10-22 add comanent list
2023-10-28 update schematic, pcb
2023-10-29 add keyboard
2023-11-03 update keyboard
2023-11-03 add 3d model
2023-11-09 update schema schematic board
2023-11-18 update keyboard schematic
2023-11-19 update UserDraw layer
2023-11-27 add some urls
2023-12-06 add output files for pcb_v0.4
2023-12-28 fix ROM switch notation
2023-12-31 improve keyboard
2023-12-31 connect virtual com port signal TX & RX to ESD diodes
2024-02-11 update stlink update ZX-keyboard updeate test
2024-02-25 update schematic add layout
2024-02-25 some updae
2024-02-25 add markup layer and markup info
2024-02-25 add ket footprint library
2024-02-25 reposition all button add stabilize
2024-02-25 add stabilizer replace mount hole
2024-02-26 update local footprints in ZX_Keyboard
2024-02-26 update Zilog library
2024-02-26 migrate to kicad8
2024-02-26 migrete to kicad8
2024-02-26 migreate to kicad8
2024-02-26 migrete licad8
2024-02-26 update button footprint
2024-02-26 Trace route
2024-02-27 migrate to kicad_8.0
2024-02-27 trace route ZX-keyboard
2024-02-28 tracing is done
2024-02-28 restore ZX-Spectrum-Keyboard_Switch.kicad_sch
2024-02-28 fix legend of button
2024-02-29 update master
2024-02-29 update pcb ZX_Keyboard
2024-02-29 update symbol ad project file
2024-02-29 update stlink
2024-02-29 migrate ZX-Spectrum-Keyboard_Switch
2024-02-29 migrate ZX-Spectrum-Keyboard to kicad_8.0
2024-02-29 migrate ZX-Spectrum-Perefiral to kicad8.0
2024-02-29 update schematic ZX-Spectrum-Pentagon
2024-02-29 migrate Spectrum-Pentagon to kicad 8.0
2024-02-29 non functional update
2024-03-01 update model for ZX-Spectrum-Keyboard & ZX_Keyboard
2024-03-01 update footprints
2024-03-01 update 3d model
2024-03-01 rename project from ZX-Spectrum-Keyboard_Switch.kicad_pcb ZX-Spectrum-Key-Panel.kicad_pcb
2024-03-02 add Controlers symbol progect
2024-03-02 use folder for multi sheet project
2024-03-02 add zxm_extrime_extension add 74XX283 to 74IEC start ZX-Spectrum-Perefiral project
2024-03-02 update FDDC
2024-03-04 migrate to KiCAD 8.0 fix schema trace pbc
2024-03-07 update library 74IEC FDController
2024-03-07 CPU.kicad_sch non functional changes update fdd controller
2024-03-08 update schematic FDC
2024-03-15 improve schematic fdc
2024-03-16 fix keyboard fix keyboard discription
2024-03-18 add fix picture
2024-03-19 fix mounting hole for ZX-Spectrum-Key-Panel improve schema fdd
2024-03-19 rename FDDC fdc
2024-03-19 add keywords for some symbol in library 74IEC update some symbol in zx_custom_symbol improve FDC, Connectors, ZX-Spectrum-Perefiral schematic
2024-04-01 update keyboard & FDC schematic
2024-04-01 change up extra [ENTER] to [E CUR]
2024-04-01 restore schematic of FDC
2024-04-01 update ZX-Spectrum-Perefiral
2024-04-02 fix 74ICE, FDControlers, edge_lib library update all schematic and board fix ERC ZX-Spectrum-Perefiral
2024-04-02 update fdc ideY
2024-04-07 FDControlers rename from VCC1 to VDD zx_custom_symbol add connector Conn_02x32_Odd_Even ZX-Spectrum-Pentagon rename from +9V to POWER ZX-Spectrum-Perefiral improve schematic
2024-04-25 add apple apple-lpc
2024-04-25 improve apple-lpc part a start apple-lpc part b
2024-05-01 update apple-lpc
2024-05-16 fix 3d model
2024-05-18 Add clone project
2024-05-18 rename some line for STM8
2024-05-23 fix path
2024-05-23 Fix RGB
2024-05-25 update trace rgb out
2024-07-05 add ZX-Spectrum-HDMI
2024-08-07 fix silk layer
2024-08-09 update silk
2024-09-16 add HDMI adapter
2024-10-05 add 3.5 mm jacck
2024-10-27 update keyboard connection
2024-10-27 new annotation
2024-10-29 add label
2024-10-30 ZX keyboard Release V1.0
2024-11-24 modefie user draw layer
2024-12-17 start beomaster_5500
2024-12-17 improve schema amplifier
2024-12-17 add right channel
2024-12-25 add capacitor foot print
2024-12-25 improve schema
2025-01-03 add 1528 mask
2025-01-04 footprint for intel BGA1528
2025-01-04 create pcb
2025-01-04 add pcb
2025-01-04 add BGA1528
2025-01-04 update template
2025-01-05 Add 3 types with 0.55, 0.50, 045 hole
2025-08-20 add lenovo power addapter
2025-08-20 refill
2025-08-21 Change footprint
